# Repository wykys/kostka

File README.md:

# Elektronická hrací kostka

(40*40)mm^2
Napájení RC2032

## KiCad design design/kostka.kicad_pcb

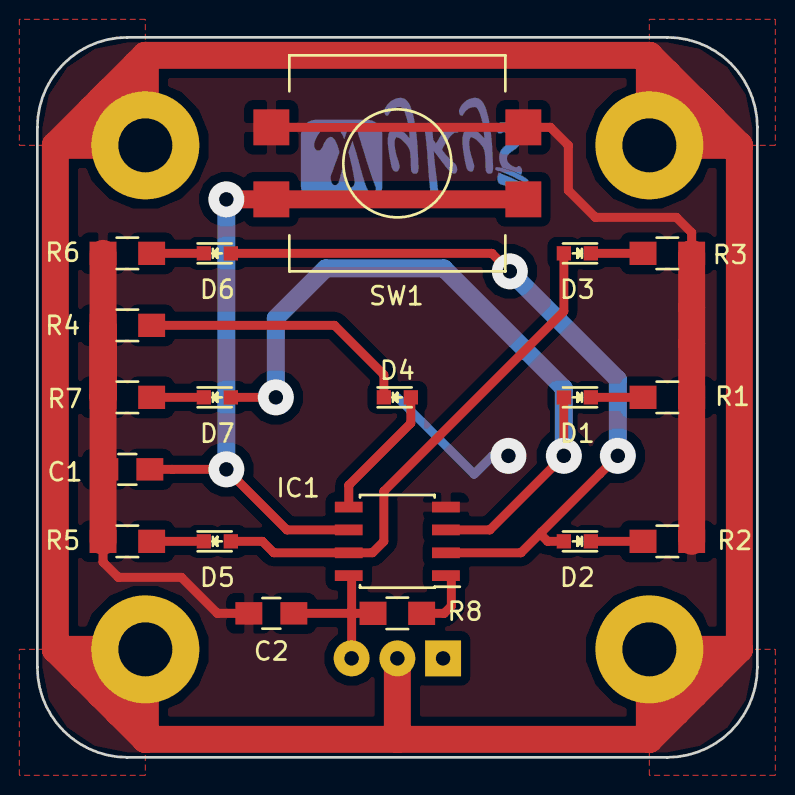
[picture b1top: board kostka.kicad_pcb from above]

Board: 2 copper layers, 40.0 x 40.0 mm, 24 parts (1 on the bottom side), 16 nets.

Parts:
C1: 10n; C_0805_HandSoldering
C2: 100n; C_0805_HandSoldering
D1, D2, D3, D4, D5, D6, D7: LED; LED_0603
IC1: ATTINY13A-SS; SOIC-8_3.9x4.9mm_Pitch1.27mm
M1, M2, M3, M4: M3; SolderWirePad_single_0-8mmDrill
R1, R2, R3, R4, R5, R6, R7: R; R_0805_HandSoldering
R8: 10k; R_0805_HandSoldering
SW1: HOD; SW_SPST_PTS645
SW2: ON-OFF; SW_Micro_SPST_Angled

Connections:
/A: D4.2, IC1.5
/B: D3.2, D5.2, IC1.7
/C: D2.2, D6.2, IC1.2
/D: D1.2, D7.2, IC1.3
GND: C1.2, C2.2, IC1.4, R1.1, R2.2, R3.1, R4.1, R5.2, R6.1, R7.1, SW1.1
unnamed: C1.1, IC1.6, SW1.2
unnamed: D1.1, R1.2
unnamed: D2.1, R2.1
unnamed: D3.1, R3.2
unnamed: D4.1, R4.2
unnamed: D5.1, R5.1
unnamed: D6.1, R6.2
unnamed: D7.1, R7.2
unnamed: IC1.1, R8.2
unnamed: M1.1, M2.1, M3.1, M4.1, SW2.2
VDD: C2.1, IC1.8, R8.1, SW2.1

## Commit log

2016-12-13 :circus_tent: Added .gitattributes
2016-12-13 init
2016-12-13 readme
2016-12-13 oprava navodu
2016-12-13 oprava
2016-12-13 oprava 2
